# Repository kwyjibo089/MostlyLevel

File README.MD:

# MostlyLevel

**A touchscreen levelling display for campervans.** A small ESP32-S3 display reads a Bluetooth tilt sensor mounted in the van and shows, live, how the van is tilted and how much to lift each wheel to get it level.

*Screens as drawn by the app (240 × 320 px, shown at 2×). The images are rendered from the app's own drawing code by the desktop tests; a screenshot taken on the device matched them.*

> **Status: working prototype.** It runs in the owner's van (a Fiat Ducato-style campervan) and is used day to day. Several things are still assumptions; see [What is verified](#what-is-verified). This README is also the project's state summary for other tools and assistants (for example, enclosure design in Claude Desktop with Fusion): it describes the code as it is on `main`.

## Contents

- [Features](#features)
- [Hardware](#hardware)
- [How it works](#how-it-works)
- [Getting started](#getting-started)
- [Using MostlyLevel](#using-mostlylevel)
- [Configuration](#configuration)
- [Development](#development)
- [What is verified](#what-is-verified)
- [Enclosure design notes](#enclosure-design-notes)
- [Towards a product](#towards-a-product)
- [Repository layout](#repository-layout)
- [License](#license)

## Features

- **Two ways to read the van's attitude** on the ATTITUDE page:
  - **VAN**: the van seen from behind tilts with roll, and seen from the right it tilts with pitch. Each stands on level ground and pivots on its lower wheel; the tilt is drawn 3× exaggerated so small slopes are visible.
  - **HORIZON**: an aircraft-style attitude indicator (moving sky and ground, pitch ladder, curved scale) with the van seen from behind as the fixed symbol.
- **Wedge advice** on the LEVELLING page: **2 WEDGES** names the two wheels to lift and by how many centimetres; **4 CORNERS** shows all four. Computed from the van's wheelbase and track widths.
- **Level indicator**: a green frame around the whole screen while pitch and roll are both within ±0.5° (with hysteresis, so it does not flicker at the edge).
- **Calibration**: hold **CALIBRATE** for one second to make the current attitude the level reference; it survives restarts.
- **Four languages**: English, German, French, Spanish, switchable on the device (hold the language button); the choice survives restarts.
- **Sensor status**: live, stale, or disconnected state and the sensor's battery level in the header, with clear warnings when data is missing.
- **Robust for long runs**: automatic Bluetooth reconnection and recovery, and the app restarts the board after repeated errors instead of freezing with a stale "level" picture.
- **Flicker-free drawing**: pages are composited off-screen in strips and sent to the display in one transfer per strip.

### Android app

An Android app in [`mobile/`](mobile/README.md) does the same job on a phone: it connects directly to the sensor and shows the same pages, with phone-sized graphics, a choice of camper type and colour, and settings for the sensor, the dimensions, and the language. It is a first version; its levelling maths and sensor decoding are tested against the ESP32 code. The sensor accepts one connection at a time, so the phone and the display cannot both be connected.

## Hardware

| Part | What is used | Notes |
| --- | --- | --- |
| Display board | ESP32-S3 2.8" display board, ES3C28P family | 240 × 320 ILI9341 IPS display on SPI, capacitive touch on I2C. Vendor documentation: [lcdwiki 2.8inch ESP32-S3 Display](https://www.lcdwiki.com/2.8inch_ESP32-S3_Display). |
| Firmware | MicroPython 1.29.0, `ESP32_GENERIC_S3` | The image in `esp32/firmware/` is byte-identical to the official download. |
| Tilt sensor | WT901BLE67-style BLE inclinometer | Sends attitude notifications over Bluetooth LE; battery powered. Configured by its BLE address in `esp32/src/config.py`. |
| Power | USB-C, 5 V | The board also has a Li-Po connector with charger (not used by the app). |

**Pin assignments** (from the vendor's board-support package, matching the app):

| Signal | GPIO |
| --- | --- |
| LCD SPI SCK / MOSI / MISO | 12 / 11 / 13 |
| LCD CS / DC / backlight | 10 / 46 / 45 |
| Touch I2C SCL / SDA, reset | 15 / 16, 18 (address `0x38`) |

The vendor documentation lists the touch controller as an FT6336G; the app talks to it with a minimal FT5x06-compatible reader. More detail, including what is unconfirmed, is in [docs/hardware.md](docs/hardware.md).

## How it works

```
WT901 sensor ──BLE notify──▶ ble_read.py ──latest sample──▶ app.py step()  (every ~30 ms)
                               ▲     │                               ├─ vehicle pitch/roll (axis mapping, calibration)
                               └─────┘ reconnect / recover           ├─ ATTITUDE: vans.py (VAN) or the horizon (HORIZON)
FT5x06 touch ──I2C──▶ touch.py ──taps, long presses────────────────▶ ├─ LEVELLING: corner lift estimates
                                                                     └─ compositor.py ──strips──▶ ili9341.py ──SPI──▶ LCD
```

- `main.py` imports `app.py` and calls `app.run()`: `setup()` once, then `step()` in a loop. BLE callbacks only store the latest sample; all drawing happens in `step()`.
- Pages are recorded as filled rectangles (plus small bitmaps for pictures such as the vans and the arc), composited into a 240 × 40 strip buffer, and sent strip by strip. Strips whose content did not change are skipped.
- The vans are vector shapes generated on the desktop (`esp32/tools/make_vans.py` → `esp32/src/van_shapes.py`) and rotated on the board with integer maths, then filled with `framebuf.poly()`.
- Screen texts come from `shared/i18n/lang_<code>.json`; only the active language is kept in memory.

More: [docs/architecture.md](docs/architecture.md) and the decision log in [docs/decisions.md](docs/decisions.md).

## Getting started

You need the display board, a WT901BLE67-style sensor, a USB-C cable, and Python 3 on your computer.

1. **Install the tools** (in the `esp32/` folder; all commands below run from there):

   ```bash
   cd esp32
   python3 -m venv .venv
   .venv/bin/python -m pip install -r requirements-dev.txt
   ```

2. **Flash MicroPython** if the board does not have it yet. This is MicroPython's standard procedure for ESP32-S3 boards; it has not been recorded for this board in the repository:

   ```bash
   .venv/bin/python -m pip install esptool
   .venv/bin/python -m esptool --chip esp32s3 erase_flash
   .venv/bin/python -m esptool --chip esp32s3 write_flash -z 0 firmware/ESP32_GENERIC_S3-20260824-v1.29.0.bin
   ```

3. **Point the app at your sensor**: set `SENSOR_MAC` in `src/config.py` to the sensor's BLE address (`src/ble_scan.py` lists nearby devices), and set your van's `WHEELBASE_MM`, `FRONT_TRACK_MM`, and `REAR_TRACK_MM`.

4. **Deploy and start**:

   ```bash
   tools/deploy.sh            # or: tools/deploy.sh -p /dev/ttyACM0
   ```

   This precompiles the app to `.mpy`, uploads only changed files, and resets the board. The display shows *WAITING FOR SENSOR* until the sensor connects.

5. **Mount and calibrate**: fix the sensor in the van, level the van with a trusted spirit level, and hold **CALIBRATE** for one second.

`esp32/tools/deploy.sh -h` lists the options (upload sources instead of `.mpy`, choose a port, open the REPL, and so on).

## Using MostlyLevel

| Page | Shows | Touch |
| --- | --- | --- |
| **ATTITUDE → VAN** | Rear view (roll) and side view (pitch) of the van, P/R readouts | Tabs switch views; hold **CALIBRATE** or the language button for 1 s |
| **ATTITUDE → HORIZON** | Virtual horizon, pitch ladder, curved scale, P/R readouts | Same as VAN |
| **LEVELLING → 2 WEDGES** | The two wheels to lift, with heights in cm, or *NO WEDGES NEEDED* | Tabs switch views |
| **LEVELLING → 4 CORNERS** | Lift for each wheel | Tabs switch views |

- **Signs**: positive pitch = front higher; positive roll = left side higher. Left and right are as seen facing forward.
- **HORIZON** follows the aircraft convention as seen from the driver's seat: with the left side high, the horizon rises on the right.
- **Lift heights** are geometric estimates (the van treated as a rigid plane, the sensor assumed at the centre of the wheel footprint). Recheck the readings after placing wedges.
- **Header**: the sensor's battery level and the connection state (LIVE, SCANNING, STALE, NO LINK, …).

## Configuration

All adjustable values live in [`esp32/src/config.py`](src/config.py), with comments saying which are tested and which are assumptions. The ones you are most likely to change:

| Setting | Default | Purpose |
| --- | --- | --- |
| `SENSOR_MAC` | the owner's sensor | BLE address of the sensor to connect to |
| `WHEELBASE_MM`, `FRONT_TRACK_MM`, `REAR_TRACK_MM` | 4035, 1810, 1790 | Van geometry for the lift estimates |
| `DISPLAY_PITCH_SIGN`, `DISPLAY_ROLL_SIGN` | 1.0 | Flip if the sensor is mounted the other way round |
| `LEVEL_FRAME_THRESHOLD_DEG`, `LEVEL_FRAME_RELEASE_THRESHOLD_DEG` | 0.5, 0.7 | When the green frame turns on and off |
| `VAN_TILT_GAIN`, `VAN_TILT_MAX_DEG` | 3.0, 20 | Exaggeration of the VAN view's tilt |
| `SCREEN_TOP_INSET` | 0 | Rows hidden by the case at the top of the display (the first case needed 10) |
| `LANGUAGES`, `DEFAULT_LANGUAGE` | en, de, fr, es; en | Languages offered by the language button |
| `LONG_PRESS_MS` | 1000 | Hold time for CALIBRATE and the language button |

Screen texts are in `shared/i18n/lang_en.json`, `lang_de.json`, `lang_fr.json`, and `lang_es.json` (shared with the planned Android app). To add a language, copy `lang_en.json` to `lang_<code>.json`, translate it (in uppercase), and add the code to `LANGUAGES`; the tests check that every text fits its space and that the font has every character.

## Development

Run these from the `esp32/` folder:

```bash
tools/test.sh                 # ruff, MicroPython compile check (mpy-cross), pytest
tools/test.sh --update-golden # after an intentional visual change; review the image diff
tools/screenshot.sh [name]    # capture the running display as ../assets/<name>.png
tools/make_vans.py            # regenerate src/van_shapes.py after editing the van shapes
tools/readme_images.sh        # refresh ../assets/ from tests/golden/
```

- **Tests** run the MicroPython sources under desktop Python with fake hardware (`esp32/tests/fakes/`: `machine`, `bluetooth`, `framebuf`, and an ILI9341 panel model that decodes the SPI commands into pixels). They cover the BLE client and decoder, levelling maths, touch, rendering invariants (composited output equals direct drawing), recovery logic, and reference images of every page and language in `esp32/tests/golden/`. Passing tests show behaviour against the fakes, not on hardware.
- **CI** (GitHub Actions, `.github/workflows/esp32.yml`) runs `esp32/tools/test.sh` for every pull request and push to `main`, then builds the `.mpy` bundle as a downloadable artifact. `main` is protected: changes go through pull requests.
- **Records**: [CHANGELOG.md](CHANGELOG.md) for changes, [docs/decisions.md](docs/decisions.md) for design decisions with their measurements.

## What is verified

| Area | State |
| --- | --- |
| Display output at 40 MHz SPI, flicker-free redraws | Confirmed by the owner on the device |
| Touch navigation, tabs, long press, language switching | Used by the owner on the device |
| BLE connection, notifications, automatic reconnect | Seen on the device; the disconnect warning was checked by switching the sensor off and on |
| Pitch/roll signs and axis mapping | Confirmed on the installed van (front up = +pitch, left up = +roll) |
| LEVELLING picks the correct wheels | Confirmed by the owner; the **accuracy** of the lift heights is not yet measured |
| Battery percentage | One data point (3.85 V = 60 %); other levels unchecked |
| Stability | Stress runs of 2–6 minutes with constant movement: no errors, steady memory (~54–76 KB free). A multi-hour run is planned |
| Calibration saved across restarts | Implemented and tested on the desktop; not yet checked on the device |
| Translations | Drafted by an AI assistant; not yet reviewed by native speakers |

## Enclosure design notes

Facts relevant to designing a case. They come from the vendor documentation unless marked otherwise; **measure the actual board before finalising a design**.

- **Board size**: 50.0 × 86.0 mm, 10.6 mm thick with the touch panel (9.1 mm without). Weight about 111 g. Four mounting holes, one in each corner.
- **Display**: 2.8" IPS, 240 × 320 px, used in **portrait** orientation with the USB-C port at the **bottom** edge.
- **Visible area**: the UI uses the display edge to edge, so the whole display area should stay visible and touchable. The first printed case hid about the top 9 pixel rows (`SCREEN_TOP_INSET` was 10); the redesigned case (2026-10-18) leaves the whole display visible, so the inset is 0. A case that covers part of the display again needs `SCREEN_TOP_INSET` set to the hidden rows.
- **Touch**: capacitive; the cover must not press on the glass, and conductive material over the panel affects touch.
- **Radio**: the ESP32-S3 talks to the sensor over Bluetooth; the vendor drawing shows an antenna area at the top edge of the board, so avoid metal there.
- **Ports and power**: USB-C (5 V) at the bottom. Typical consumption about 140 mA with the display on.
- **Sensor**: a separate battery-powered unit, mounted level and fixed in the van, within Bluetooth range of the display.

## Towards a product

Things to settle before selling MostlyLevel devices (a technical checklist, not legal advice):

- **Per-device setup**: the sensor's BLE address, van geometry, and sensor orientation are currently set in `esp32/src/config.py`. Customers need an on-device setup flow: pairing by scanning for the sensor, entering the wheelbase and track widths, and choosing the mounting direction.
- **Measured accuracy**: check the lift estimates against real wedge heights, and the battery bands at more levels.
- **Long-run test**: an overnight run with the real sensor.
- **Licences and notices**: the device firmware contains MicroPython (MIT), components under Apache-2.0, and Adafruit-derived code under BSD. Their notices must ship with each device, for example in the printed manual or on the product page; see [THIRD_PARTY_NOTICES.md](THIRD_PARTY_NOTICES.md).
- **Branding**: the van drawing is styled after a Fiat Ducato but carries no logo. Using "Fiat" or "Ducato" in product names or marketing touches their trademarks.
- **Compliance**: electronics sold in the EU, UK, Switzerland, or US generally need conformity marking (CE, UKCA, FCC) and safety documentation for the complete product, even when the radio module is already certified.

## Repository layout

| Path | Contents |
| --- | --- |
| `esp32/src/main.py`, `esp32/src/app.py` | Entry point; the app: pages, touch handling, main loop |
| `esp32/src/ble_read.py` | BLE client, packet decoder, reconnection and recovery |
| `esp32/src/vans.py`, `esp32/src/van_shapes.py` | Tilted van drawing; generated van shapes |
| `esp32/src/compositor.py` | Off-screen strip compositing and bitmaps |
| `esp32/src/graphics.py`, `esp32/src/ili9341.py`, `esp32/src/touch.py` | Drawing helpers and font, display driver, touch reader |
| `esp32/src/i18n.py` | Language loading |
| `esp32/src/config.py` | All settings |
| `esp32/src/screenshot.py`, `esp32/src/ble_scan.py` | Screenshot writer; standalone BLE scan diagnostic |
| `esp32/tests/` | Desktop tests, fake hardware, reference images |
| `esp32/tools/` | Deploy, build, test, screenshot, van-shape, and README-image scripts |
| `esp32/firmware/` | The MicroPython firmware image and its licence |
| `esp32/reference/esp32_s3_es3c28p/` | The vendor's ESP-IDF board-support package, kept as reference only (not used by the app) |
| `esp32/pyproject.toml`, `esp32/requirements-dev.txt` | Desktop tooling: pytest, ruff, mpy-cross |
| `esp32/tools/make_fixtures.py` | Writes `shared/fixtures/`: the ESP32 logic's results that the Android app is tested against |
| `shared/i18n/lang_*.json` | The ESP32's screen texts (all caps for its font) |
| `shared/fixtures/` | Reference results of the ESP32 decoder and levelling maths, generated; see `mobile/README.md` |
| `mobile/` | The Android app (React Native, Expo) with the same functionality as the display; see [mobile/README.md](mobile/README.md) |
| `hardware/` | KiCad project for the custom PCB: schematic, layout, footprints, BOM, fabrication files, vendor data |
| `case/` | Enclosure design files (empty so far) |
| `docs/` | Architecture, hardware, and decision records |
| `assets/` | README images and screenshots |

## License

MostlyLevel's own code is licensed under the [MIT License](LICENSE). The ILI9341 initialisation values and the bitmap font come from Adafruit's BSD-licensed libraries, the firmware image is MicroPython (MIT, with bundled components under their own licences), and `esp32/reference/` is Espressif's Apache-2.0 board-support code. Details and the required notices are in [THIRD_PARTY_NOTICES.md](THIRD_PARTY_NOTICES.md).

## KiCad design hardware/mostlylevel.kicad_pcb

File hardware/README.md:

# Hardware

KiCad project for the MostlyLevel PCB (revision A). Open `mostlylevel.kicad_pro` in KiCad.

| Path | Contents |
| --- | --- |
| `mostlylevel.kicad_sch`, `mostlylevel.kicad_pcb` | Schematic and board layout |
| `mostlylevel.pretty/` | Project footprints |
| `mostlylevel_schematic.pdf`, `mostlylevel.png` | Exported schematic and board image |
| `bom/` | Bill of materials for JLCPCB |
| `fab/revA/` | Gerbers, drill files, BOM, and placement (CPL) for fabrication, plus the Gerbers as one zip for upload |
| `review/` | Renders and exports for design review |
| `routing/` | DRC reports of each routing pass (`drc1.json` … `drc12.json`, latest last), copper layer drawings (`fcu.svg`, `bcu.svg`), and the board before the reroute (`mostlylevel_before_reroute.kicad_pcb`) |
| `vendor/` | Placement and routing drawings; vendor downloads for the display board are kept locally, not in git |

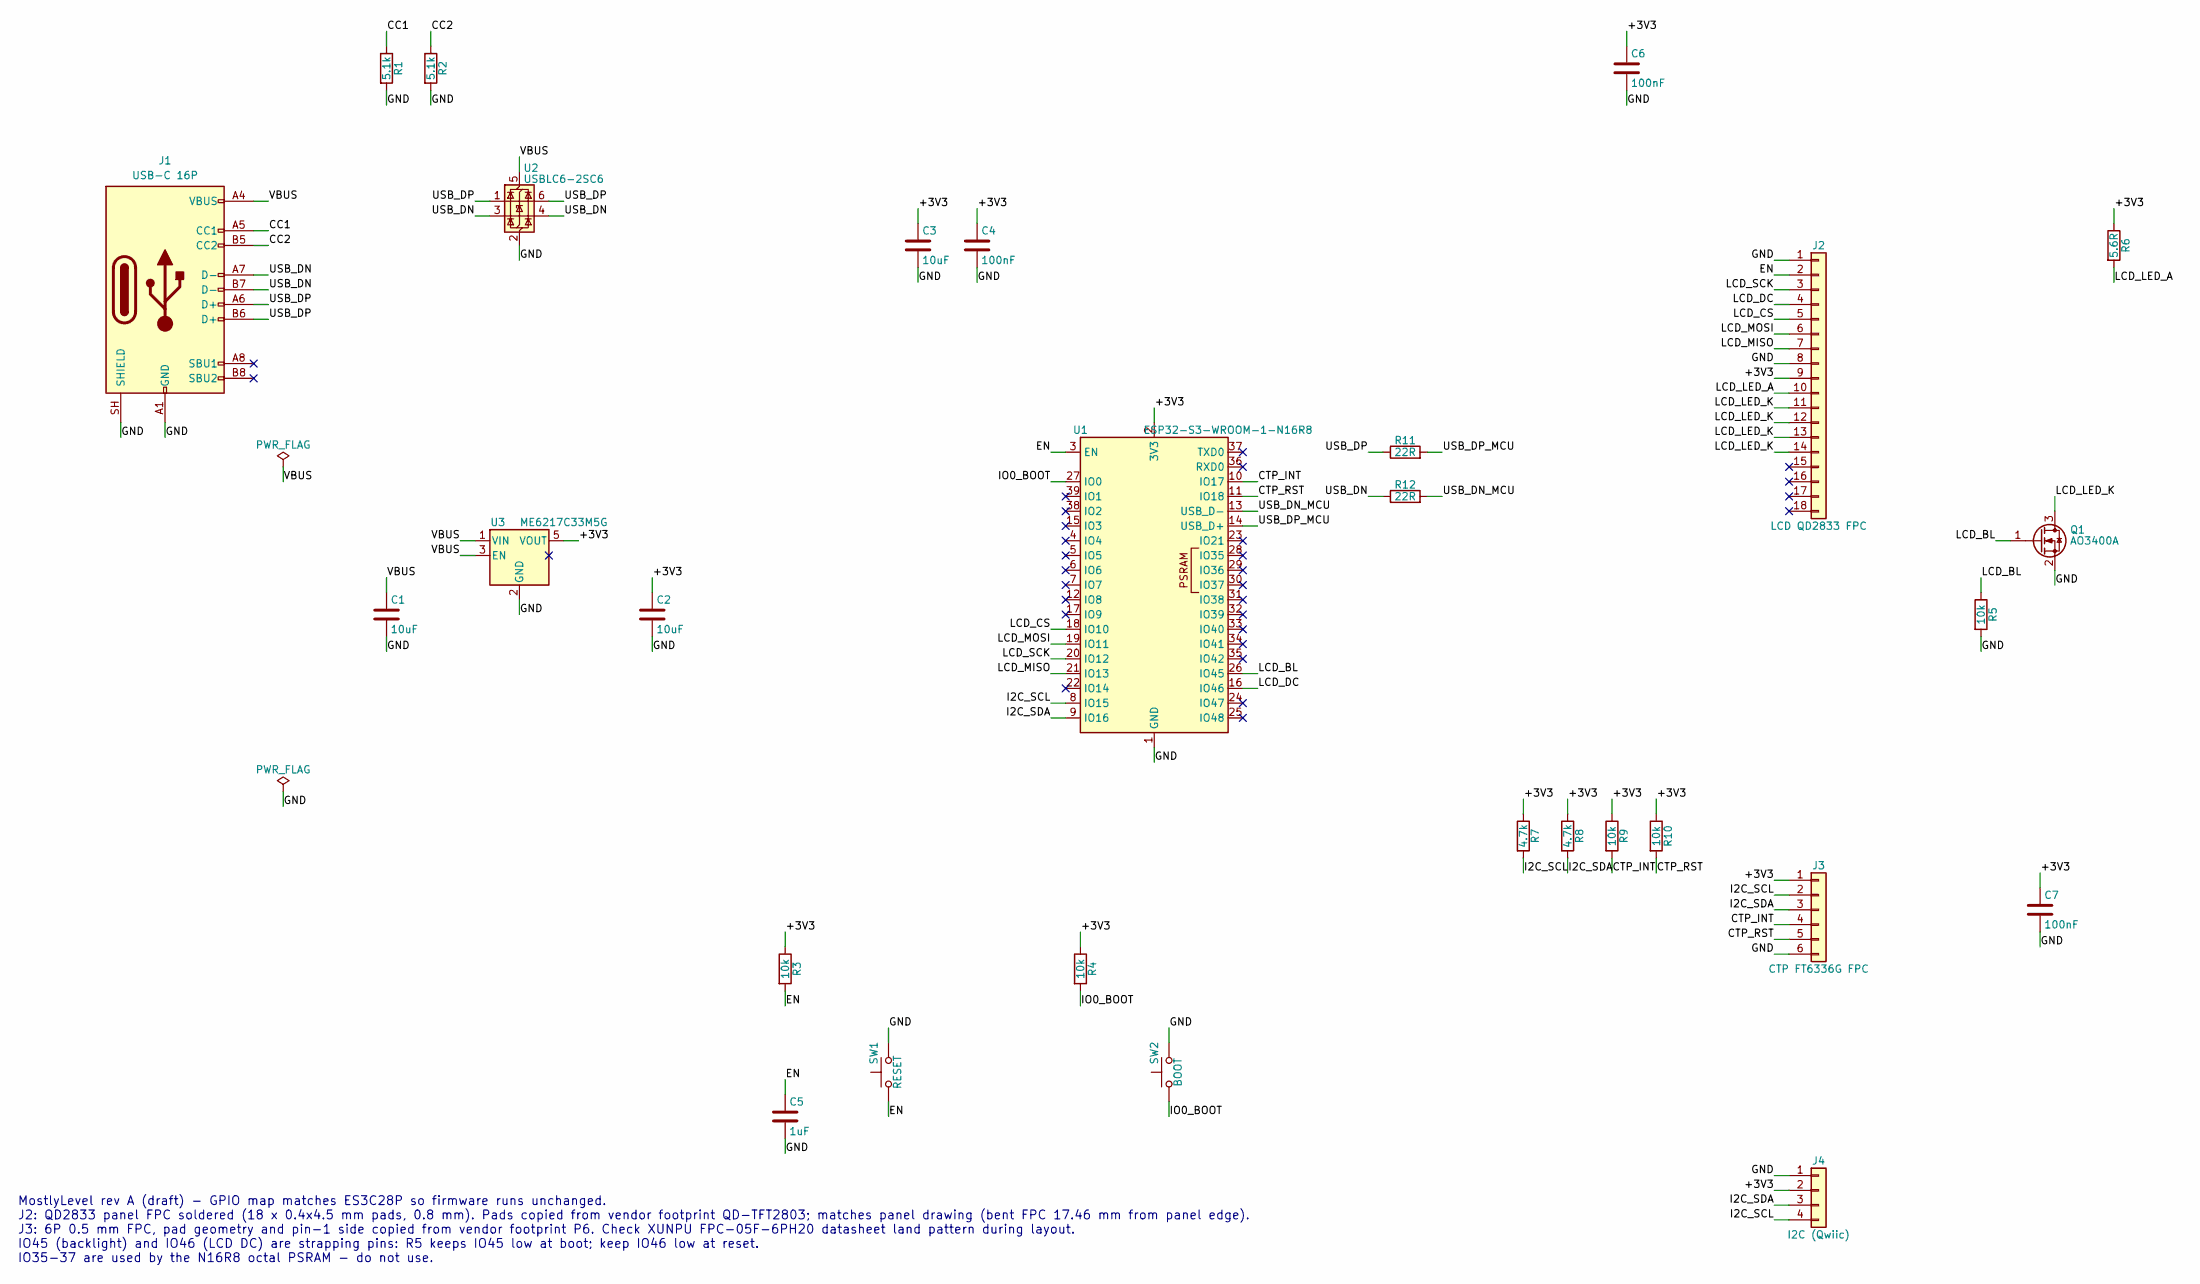
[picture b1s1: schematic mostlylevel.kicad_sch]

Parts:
C1, C2, C3: 10uF; C_0805_2012Metric; MPN CL21A106KAYNNNE; LCSC C15850
C4, C6, C7: 100nF; C_0402_1005Metric; MPN CL05B104KO5NNNC; LCSC C1525
C5: 1uF; C_0402_1005Metric; MPN CL05A105KA5NQNC; LCSC C52923
J1: USB-C 16P; USB_C_Receptacle_HRO_TYPE-C-31-M-12; MPN TYPE-C-31-M-12; LCSC C165948
J2: LCD QD2833 FPC; QD2833_LCD_FPC_18P_P0.80mm_Vendor; MPN QD2833 2.8in IPS panel (vendor FPC240A8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
J3: CTP FT6336G FPC; FPC_0.5mm_6P_H2.0_Vendor; MPN FPC-05F-6PH20; LCSC C2856796
J4: I2C (Qwiic); JST_SH_SM04B-SRSS-TB_1x04-1MP_P1.00mm_Horizontal; MPN SM04B-SRSS-TB(LF)(SN); LCSC C160404
Q1: AO3400A; SOT-23; MPN AO3400A; LCSC C20917
R1, R2: 5.1k; R_0402_1005Metric; MPN 0402WGF5101TCE; LCSC C25905
R3, R4, R5, R9, R10: 10k; R_0402_1005Metric; MPN 0402WGF1002TCE; LCSC C25744
R6: 5.6R; R_0603_1608Metric; MPN FRC0603F5R60TS; LCSC C2933244
R7, R8: 4.7k; R_0402_1005Metric; MPN 0402WGF4701TCE; LCSC C25900
R11, R12: 22R; R_0402_1005Metric; MPN 0402WGF220JTCE; LCSC C25092
SW1: RESET; SW_Push_1P1T_XKB_TS-1187A; MPN TS-1187A-B-A-B; LCSC C318884
SW2: BOOT; SW_Push_1P1T_XKB_TS-1187A; MPN TS-1187A-B-A-B; LCSC C318884
U1: ESP32-S3-WROOM-1-N16R8; ESP32-S3-WROOM-1_Via0.3; MPN ESP32-S3-WROOM-1-N16R8; LCSC C2913202
U2: USBLC6-2SC6; SOT-23-6; MPN USBLC6-2SC6; LCSC C7519
U3: ME6217C33M5G; SOT-23-5; MPN ME6217C33M5G; LCSC C427602

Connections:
/+3V3: C2.1, C3.1, C4.1, C6.1, C7.1, J2.9, J3.1, J4.2, R3.1, R4.1, R6.1, R7.1, R8.1, R9.1, R10.1, U1.2 (3V3), U3.5 (VOUT)
/CC1: J1.A5 (CC1), R1.1
/CC2: J1.B5 (CC2), R2.1
/CTP_INT: J3.4, R9.2, U1.10 (IO17)
/CTP_RST: J3.5, R10.2, U1.11 (IO18)
/EN: C5.1, J2.2, R3.2, SW1.1, U1.3 (EN)
/GND: C1.2, C2.2, C3.2, C4.2, C5.2, C6.2, C7.2, J1.A1 (GND), J1.A12 (GND), J1.B1 (GND), J1.B12 (GND), J1.SH (SHIELD), J2.1, J2.8, J3.6, J4.1, Q1.2 (S), R1.2, R2.2, R5.2, SW1.2, SW2.2, U1.1 (GND), U1.40 (GND), U1.41 (GND), U2.2 (GND), U3.2 (GND)
/I2C_SCL: J3.2, J4.4, R7.2, U1.8 (IO15)
/I2C_SDA: J3.3, J4.3, R8.2, U1.9 (IO16)
/IO0_BOOT: R4.2, SW2.1, U1.27 (IO0)
/LCD_BL: Q1.1 (G), R5.1, U1.26 (IO45)
/LCD_CS: J2.5, U1.18 (IO10)
/LCD_DC: J2.4, U1.16 (IO46)
/LCD_LED_A: J2.10, R6.2
/LCD_LED_K: J2.11, J2.12, J2.13, J2.14, Q1.3 (D)
/LCD_MISO: J2.7, U1.21 (IO13)
/LCD_MOSI: J2.6, U1.19 (IO11)
/LCD_SCK: J2.3, U1.20 (IO12)
/USB_DN: J1.A7 (D-), J1.B7 (D-), R12.1, U2.3 (I/O2), U2.4 (I/O2)
/USB_DN_MCU: R12.2, U1.13 (USB_D-)
/USB_DP: J1.A6 (D+), J1.B6 (D+), R11.1, U2.1 (I/O1), U2.6 (I/O1)
/USB_DP_MCU: R11.2, U1.14 (USB_D+)
/VBUS: C1.1, J1.A4 (VBUS), J1.A9 (VBUS), J1.B4 (VBUS), J1.B9 (VBUS), U2.5 (VBUS), U3.1 (VIN), U3.3 (EN)

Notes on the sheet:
MostlyLevel rev A (draft) - GPIO map matches ES3C28P so firmware runs unchanged. J2: QD2833 panel FPC soldered (18 x 0.4x4.5 mm pads, 0.8 mm). Pads copied from vendor footprint QD-TFT2803; matches panel drawing (bent FPC 17.46 mm from panel edge). J3: 6P 0.5 mm FPC, pad geometry and pin-1 side copi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

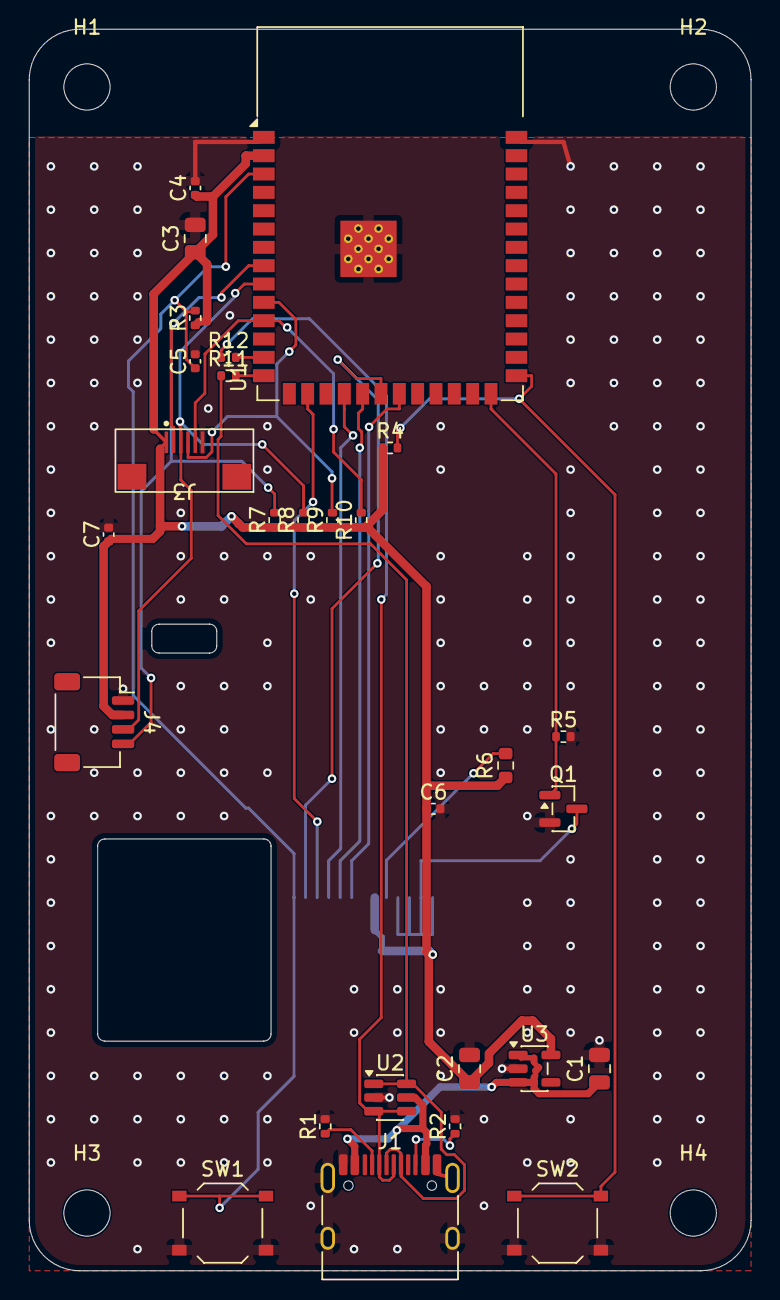
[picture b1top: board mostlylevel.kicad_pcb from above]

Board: 2 copper layers, 50.0 x 86.0 mm, 33 parts (1 on the bottom side), 23 nets.

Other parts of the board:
H1, H2, H3, H4: MountingHole_3.2mm_M3

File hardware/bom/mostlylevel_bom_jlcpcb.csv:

"Comment","Designator","Footprint","JLCPCB Part #","MPN","Manufacturer","Qty"
"10uF","C1-C3","Capacitor_SMD:C_0805_2012Metric","C15850","CL21A106KAYNNNE","","3"
"100nF","C4,C6,C7","Capacitor_SMD:C_0402_1005Metric","C1525","CL05B104KO5NNNC","","3"
"1uF","C5","Capacitor_SMD:C_0402_1005Metric","C52923","CL05A105KA5NQNC","","1"
"USB-C 16P","J1","Connector_USB:USB_C_Receptacle_HRO_TYPE-C-31-M-12","C165948","TYPE-C-31-M-12","HRO","1"
"LCD QD2833 FPC","J2","mostlylevel:QD2833_LCD_FPC_18P_P0.80mm_Vendor","","QD2833 2.8in IPS panel (vendor FPC240A8230-V1-E), hand-soldered","Hand-solder, not assembled","1"
"CTP FT6336G FPC","J3","mostlylevel:FPC_0.5mm_6P_H2.0_Vendor","C2856796","FPC-05F-6PH20","XUNPU","1"
"I2C (Qwiic)","J4","Connector_JST:JST_SH_SM04B-SRSS-TB_1x04-1MP_P1.00mm_Horizontal","C160404","SM04B-SRSS-TB(LF)(SN)","JST","1"
"AO3400A","Q1","Package_TO_SOT_SMD:SOT-23","C20917","AO3400A","Alpha & Omega","1"
"5.1k","R1,R2","Resistor_SMD:R_0402_1005Metric","C25905","0402WGF5101TCE","","2"
"10k","R3-R5,R9,R10","Resistor_SMD:R_0402_1005Metric","C25744","0402WGF1002TCE","","5"
"5.6R","R6","Resistor_SMD:R_0603_1608Metric","C2933244","FRC0603F5R60TS","","1"
"4.7k","R7,R8","Resistor_SMD:R_0402_1005Metric","C25900","0402WGF4701TCE","","2"
"RESET","SW1","Button_Switch_SMD:SW_Push_1P1T_XKB_TS-1187A","C318884","TS-1187A-B-A-B","XKB","1"
"BOOT","SW2","Button_Switch_SMD:SW_Push_1P1T_XKB_TS-1187A","C318884","TS-1187A-B-A-B","XKB","1"
"ESP32-S3-WROOM-1-N16R8","U1","RF_Module:ESP32-S3-WROOM-1","C2913202","ESP32-S3-WROOM-1-N16R8","Espressif","1"
"USBLC6-2SC6","U2","Package_TO_SOT_SMD:SOT-23-6","C7519","USBLC6-2SC6","STMicroelectronics","1"
"ME6217C33M5G","U3","Package_TO_SOT_SMD:SOT-23-5","C427602","ME6217C33M5G","Microne","1"

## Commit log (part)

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2026-05-09 first working version
2026-05-11 updated main.py and readme.md

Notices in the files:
README.MD:
License: MIT
